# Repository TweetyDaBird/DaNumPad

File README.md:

## Notice!!! 
#### DaNumPad is currently under active development! Clone/Build at your own peril! Update will follow when the design has been fully build-tested!

# DaNumPad
A 'family' of mechanical numpad/macro pads that can be configured either as a classic 17-key numpad, or as a 20 key (5x4) macro pad.

- USB-C connector
- Cherry MX compatible switches
- Kailh Hotswap sockets
- Supports PCB-mounted Cherry style stabilizers
- Designed as a companion to most 60% keyboards, being the same 5 row 'height'.
- Sandwich case with top and bottom plate from FR4 material.
- Full SMD design, adapted to easily allow both SMT manufacturing and handsoldering.

## DaNumPad unWired & DaNumPad Glow
Available as two variations, wired and wireless with identical footprint, using the same plate but different PCB.

#### DaNumPad 17 Glow
- Classic 17-Key Numpad layout
- Atmega32u4 MCU
- Full Per-Key RGB
- QMK compatible

#### DaNumPad 20 Glow
- 20-Key macropad with two optional spots for rotary encoders.
- Atmega32u4 MCU
- Full Per-Key RGB
- QMK compatible

#### DaNumPad unWired
- 20-Key macropad with two optional spots for rotary encoders.
- Optional 17-Key layout on the same PCB (Requires soldering hotswap sockets on alternate placing)
- Wireless using an nRF85420 MCU
- ZMK compatible (Bluetooth)
- Can use a QMK compatible, 2.4Ghz Wireless dongle for lower latency/battery consumption. (Under development!)

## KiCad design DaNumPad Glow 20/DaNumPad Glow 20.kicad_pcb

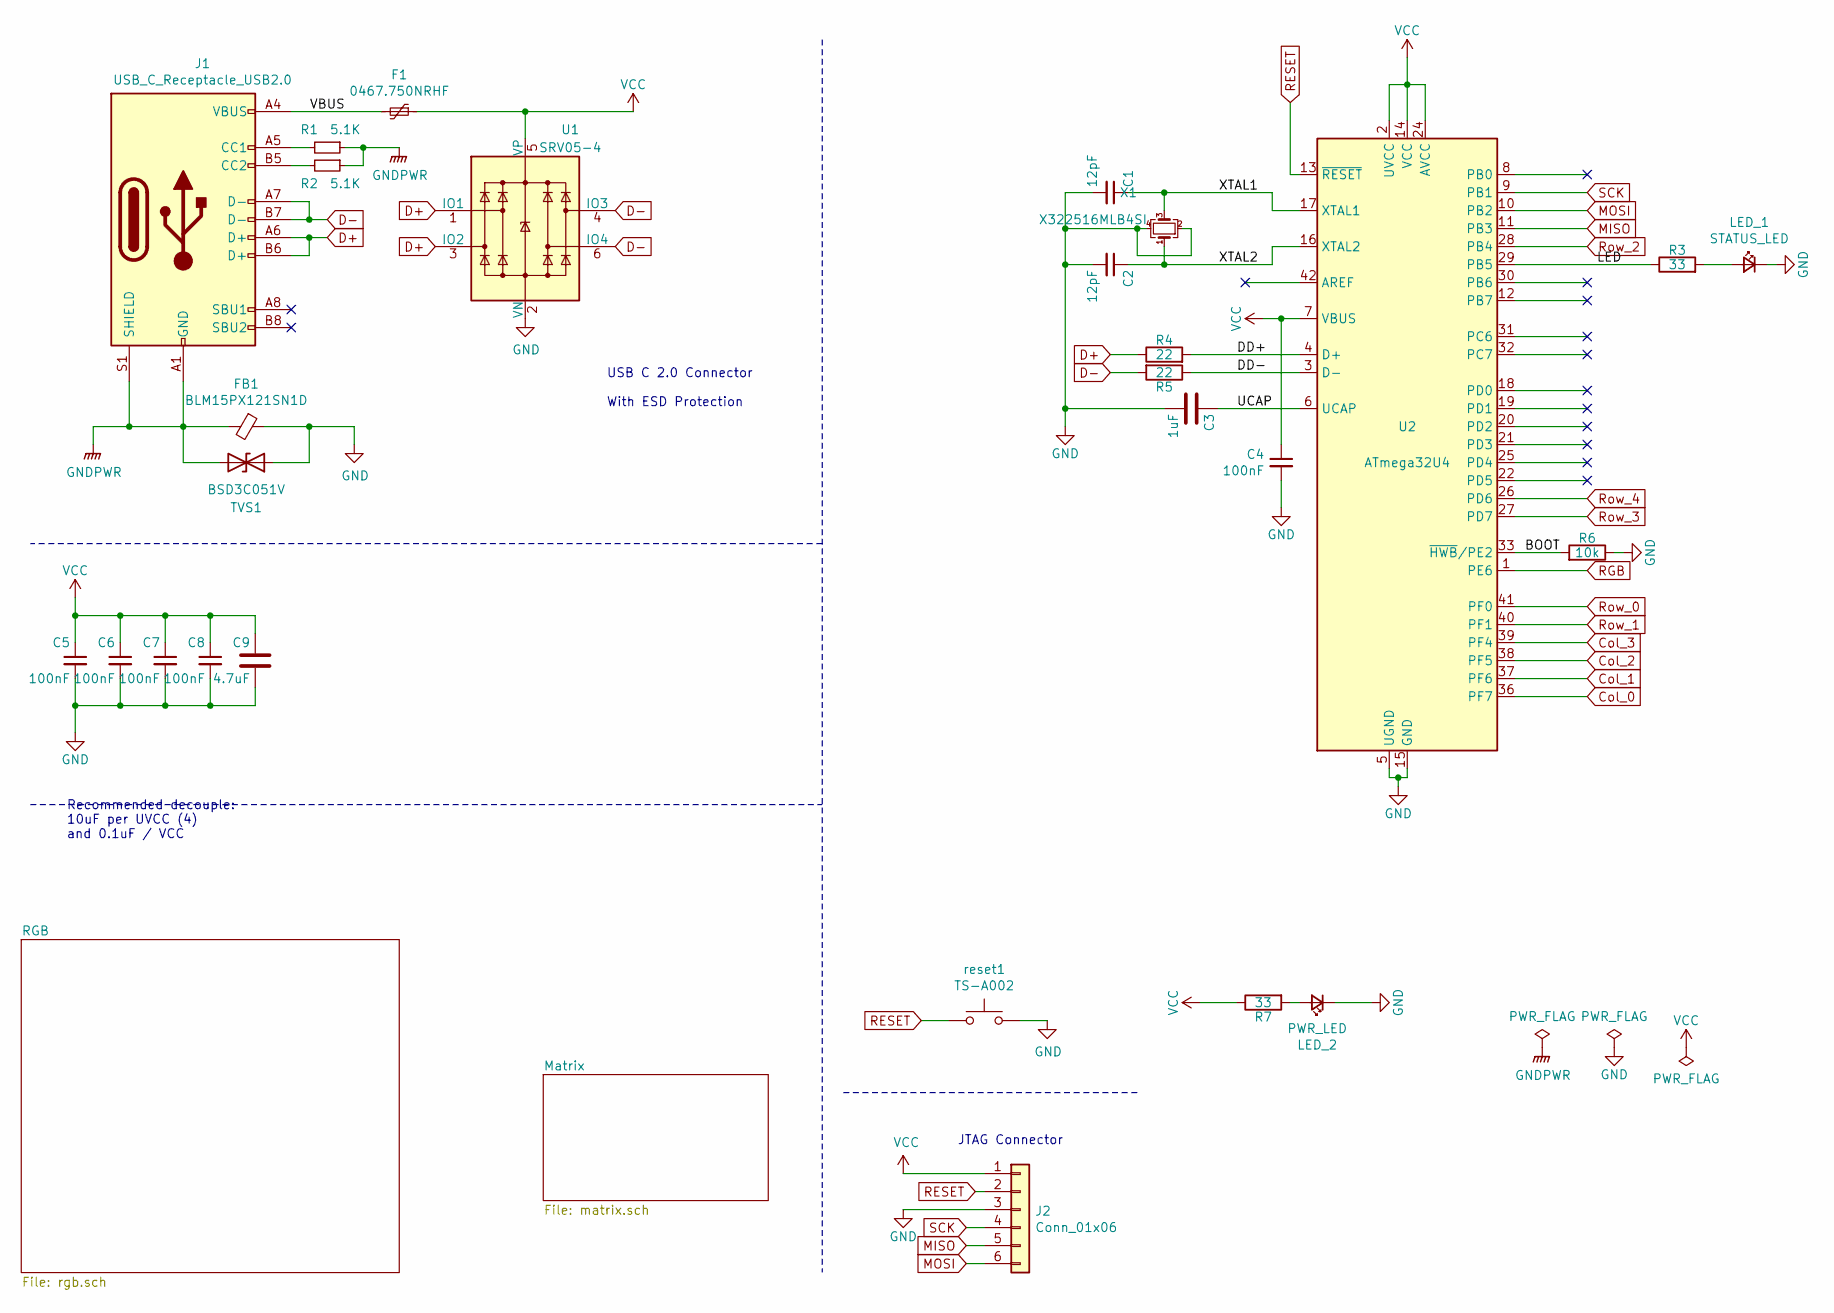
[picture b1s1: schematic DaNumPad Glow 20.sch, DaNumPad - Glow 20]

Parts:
C1, C2: 12pF; C_0603_1608Metric; Manufacturer_Part_Number CL10C120JB8NNNC; Mouser Part Number 581-06035A220J
C3: 1uF; C_0805_2012Metric; Manufacturer_Part_Number CL21B105KBFNNNE; Mouser Part Number 187-CL21B105KBFNNNG
C4, C5, C6, C7, C8: 100nF; C_0603_1608Metric; Manufacturer_Part_Number CC0603KRX7R9BB104; Mouser Part Number 581-06035C104JAT2A
C9: 4.7uF; C_0805_2012Metric; Manufacturer_Part_Number CL21A475KAQNNNE; Mouser Part Number 810-C2012X7R475K125C
F1: 0467.750NRHF; Fuse_0603_1608Metric_Castellated; Manufacturer_Part_Number 0467.750NRHF; LCSC C206991
FB1: BLM15PX121SN1D; R_0402_1005Metric_Pad0.72x0.64mm_HandSolder; Manufacturer_Part_Number BLM15PX121SN1D11; LCSC C88970
J1: USB_C_Receptacle_USB2.0; USB_C_Receptacle_HRO_TYPE-C-31-M-12; Manufacturer_Part_Number TYPE-C-31-M-12; LCSC C165948
J2: Conn_01x06; PinHeader_2x03_P2.54mm_Vertical
LED_1: STATUS_LED; LED_0603_1608Metric; Manufacturer_Part_Number KT-0603R; Mouser Part Number 604-APT1608EC
LED_2: PWR_LED; LED_0603_1608Metric; Manufacturer_Part_Number KT-0603R; Mouser Part Number 604-APT1608EC
R1, R2: 5.1K; R_0603_1608Metric; Manufacturer_Part_Number 0603WAF5101T5E; LCSC C23186
R3, R7: 33; R_0603_1608Metric; Manufacturer_Part_Number 0603WAF330JT5E; Mouser Part Number 667-ERJ-3EKF33R0V
R4, R5: 22; R_0603_1608Metric; Manufacturer_Part_Number 0603WAF220JT5E; Mouser Part Number 667-ERJ-3GEYJ220V
R6: 10k; R_0603_1608Metric; Manufacturer_Part_Number 0603WAF1002T5E; Mouser Part Number 667-ERJ-3GEYJ103V
TVS1: BSD3C051V; D_SOD-323; Manufacturer_Part_Number BSD3C051V; LCSC C151996
U1: SRV05-4; SOT-23-6; Manufacturer_Part_Number SRV05-4-P-T7; LCSC C85364
U2: ATmega32U4; QFN-44-1EP_7x7mm_P0.5mm_EP5.15x5.15mm; Manufacturer_Part_Number ATMEGA32U4-MU; Mouser Part Number 556-ATMEGA32U4RC-MU
X1: X322516MLB4SI; Crystal_SMD_3225-4Pin_3.2x2.5mm_HandSoldering; Mouser Part Number 81-XRCGB16M000FXN00R
reset1: TS-A002; SW_SPST_CK_RS282G05A3

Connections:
/BOOT: R6.2, U2.33 (~HWB~/PE2)
/DD+: R4.2, U2.4 (D+)
/DD-: R5.1, U2.3 (D-)
/LED: R3.1, U2.29 (PB5)
/UCAP: C3.1, U2.6 (UCAP)
/VBUS: F1.2, J1.A4 (VBUS), J1.A9 (VBUS), J1.B4 (VBUS), J1.B9 (VBUS)
/XTAL1: C1.1, U2.17 (XTAL1), X1.3
/XTAL2: C2.1, U2.16 (XTAL2), X1.1
Col_0: U2.36 (PF7); also elsewhere on the board
Col_1: U2.37 (PF6); also elsewhere on the board
Col_2: U2.38 (PF5); also elsewhere on the board
D+: J1.A6 (D+), J1.B6 (D+), R4.1, U1.1 (IO1), U1.3 (IO2)
D-: J1.A7 (D-), J1.B7 (D-), R5.2, U1.4 (IO3), U1.6 (IO4)
GND: C1.2, C2.2, C3.2, C4.2, C5.2, C6.2, C7.2, C8.2, C9.2, FB1.1, J2.3, LED_1.1 (K), LED_2.1 (K), R6.1, TVS1.1 (A1), U1.2 (VN), U2.5 (UGND), U2.15 (GND), U2.23 (GND), U2.35 (GND), U2.43 (GND), X1.2, X1.4, reset1.2; also elsewhere on the board
GNDPWR: FB1.2, J1.A1 (GND), J1.A12 (GND), J1.B1 (GND), J1.B12 (GND), J1.S1 (SHIELD), R1.1, R2.1, TVS1.2 (A2)
MISO: J2.5, U2.11 (PB3)
MOSI: J2.6, U2.10 (PB2)
unnamed: J1.A5 (CC1), R1.2
unnamed: J1.B5 (CC2), R2.2
unnamed: LED_1.2 (A), R3.2
unnamed: LED_2.2 (A), R7.2
RESET: J2.2, U2.13 (~RESET), reset1.1
RGB: U2.1 (PE6); also elsewhere on the board
Row_0: U2.41 (PF0); also elsewhere on the board
Row_1: U2.40 (PF1); also elsewhere on the board
Row_2: U2.28 (PB4); also elsewhere on the board
Row_3: U2.27 (PD7); also elsewhere on the board
Row_4: U2.26 (PD6); also elsewhere on the board
SCK: J2.4, U2.9 (PB1)
VCC: C4.1, C5.1, C6.1, C7.1, C8.1, C9.1, F1.1, J2.1, R7.1, U1.5 (VP), U2.2 (UVCC), U2.7 (VBUS), U2.14 (VCC), U2.24 (AVCC), U2.34 (VCC), U2.44 (AVCC); also elsewhere on the board

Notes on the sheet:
USB C 2.0 Connector With ESD Protection
Recommended decouple: 10uF per UVCC (4) and 0.1uF / VCC
JTAG Connector

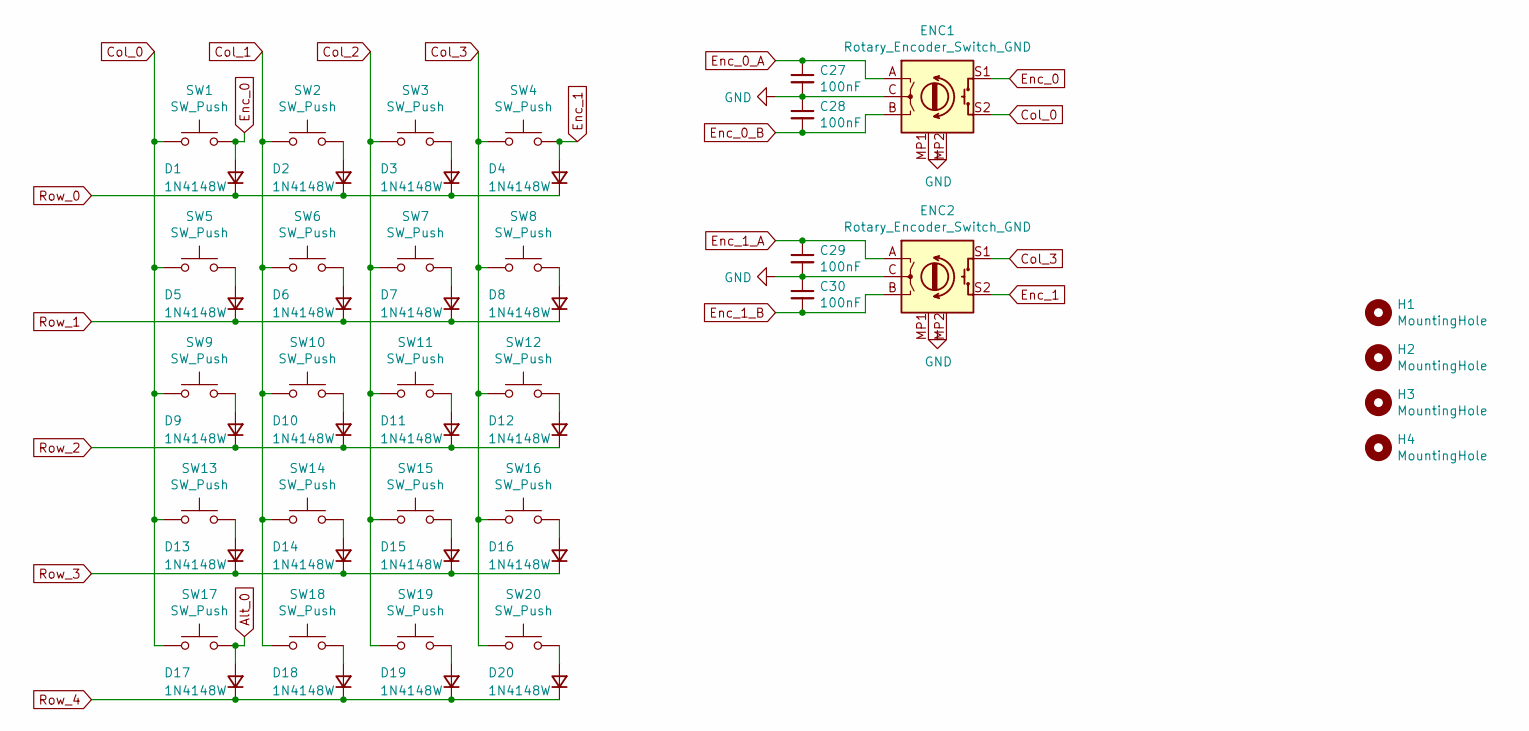
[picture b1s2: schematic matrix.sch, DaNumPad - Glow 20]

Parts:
C27, C28, C29, C30: 100nF; C_0603_1608Metric; Manufacturer_Part_Number CC0603KRX7R9BB104; LCSC C14663
D1, D2, D3, D4, D5, D6, D7, D8, D9, D10, D11, D12, D13, D14, D15, D16, D17, D18, D19, D20: 1N4148W; D_SOD-123; Manufacturer_Part_Number 1N4148W; LCSC C81598
ENC1, ENC2: Rotary_Encoder_Switch_GND; RotaryEncoder_Alps_EC11E-Switch_Vertical_H20mm
H1, H2, H3, H4: MountingHole; MountingHole_3.7mm
SW1, SW2, SW3, SW4, SW5, SW6, SW7, SW8, SW9, SW10, SW11, SW12, SW13, SW14, SW15, SW16, SW17, SW18, SW19, SW20: SW_Push; Kailh_socket_MX_RGB

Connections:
Alt_0: D17.2 (A), SW17.2
Col_0: ENC1.S2, SW1.1, SW5.1, SW9.1, SW13.1, SW17.1; also elsewhere on the board
Col_1: SW2.1, SW6.1, SW10.1, SW14.1, SW18.1; also elsewhere on the board
Col_2: SW3.1, SW7.1, SW11.1, SW15.1, SW19.1; also elsewhere on the board
Enc_0: D1.2 (A), ENC1.S1, SW1.2
Enc_0_A: C27.1, ENC1.A
Enc_0_B: C28.2, ENC1.B
Enc_1_A: C29.1, ENC2.A
Enc_1_B: C30.2, ENC2.B
GND: C27.2, C28.1, C29.2, C30.1, ENC1.C, ENC1.MP2 (GND), ENC2.C, ENC2.MP2 (GND); also elsewhere on the board
unnamed: D2.2 (A), SW2.2
unnamed: D3.2 (A), SW3.2
unnamed: D5.2 (A), SW5.2
unnamed: D6.2 (A), SW6.2
unnamed: D7.2 (A), SW7.2
unnamed: D9.2 (A), SW9.2
unnamed: D10.2 (A), SW10.2
unnamed: D11.2 (A), SW11.2
unnamed: D12.2 (A), SW12.2
unnamed: D13.2 (A), SW13.2
unnamed: D14.2 (A), SW14.2
unnamed: D15.2 (A), SW15.2
unnamed: D18.2 (A), SW18.2
unnamed: D19.2 (A), SW19.2
unnamed: D20.2 (A), SW20.2
Row_0: D1.1 (K), D2.1 (K), D3.1 (K), D4.1 (K); also elsewhere on the board
Row_1: D5.1 (K), D6.1 (K), D7.1 (K), D8.1 (K); also elsewhere on the board
Row_2: D9.1 (K), D10.1 (K), D11.1 (K), D12.1 (K); also elsewhere on the board
Row_3: D13.1 (K), D14.1 (K), D15.1 (K), D16.1 (K); also elsewhere on the board
Row_4: D17.1 (K), D18.1 (K), D19.1 (K), D20.1 (K); also elsewhere on the board

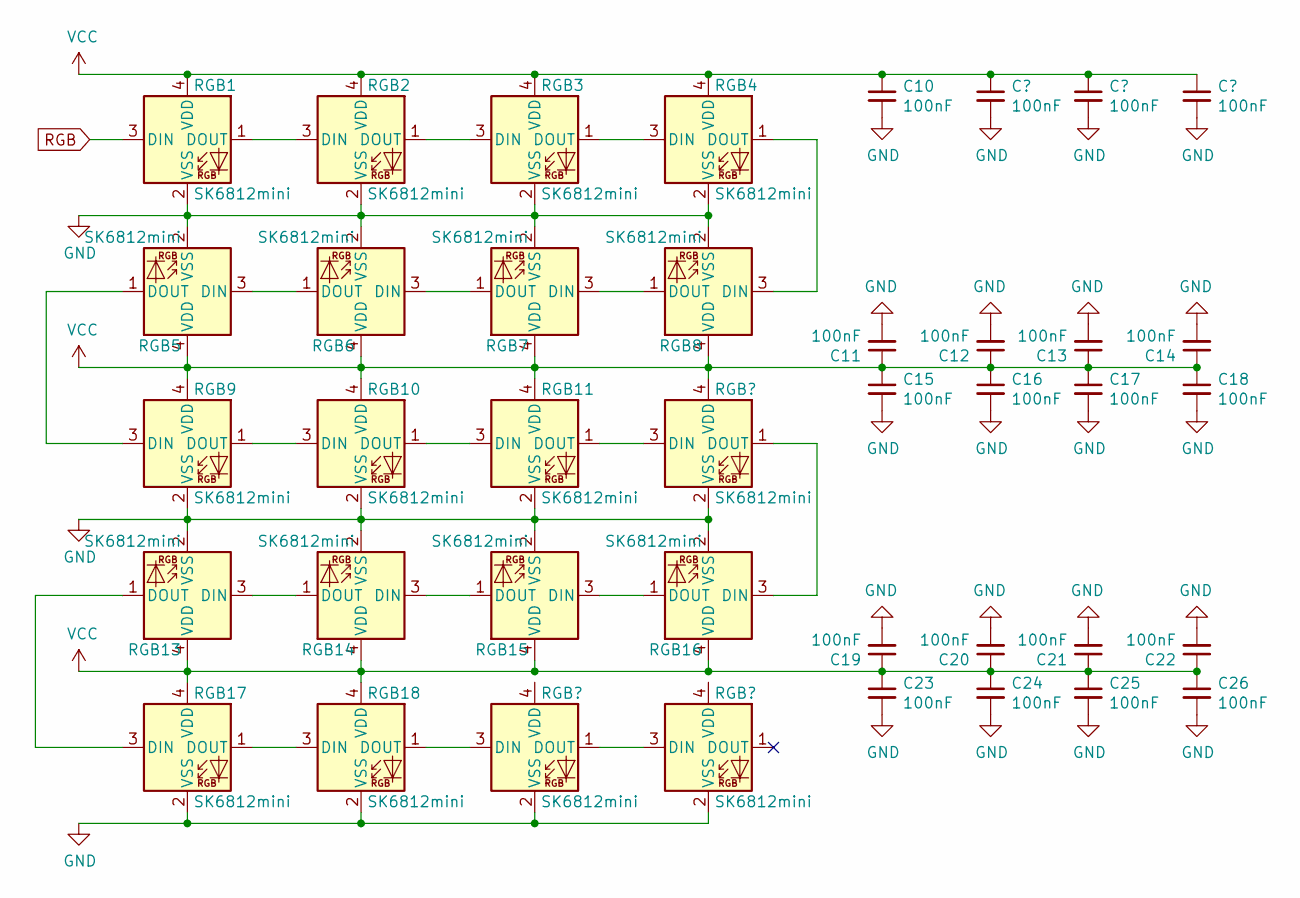
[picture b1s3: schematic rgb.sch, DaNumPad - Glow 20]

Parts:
C10, C11, C12, C13, C14, C15, C16, C17, C18, C19, C20, C21, C22, C23, C24, C25, C26: 100nF; C_0603_1608Metric; Manufacturer_Part_Number CC0603KRX7R9BB104; LCSC C14663
RGB1, RGB2, RGB3, RGB4, RGB5, RGB6, RGB7, RGB8, RGB9, RGB10, RGB11, RGB13, RGB14, RGB15, RGB16, RGB17, RGB18: SK6812mini; SK6812MINI_Midmount

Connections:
GND: C10.2, C11.2, C12.2, C13.2, C14.2, C15.2, C16.2, C17.2, C18.2, C19.2, C20.2, C21.2, C22.2, C23.2, C24.2, C25.2, C26.2, RGB1.2 (VSS), RGB2.2 (VSS), RGB3.2 (VSS), RGB4.2 (VSS), RGB5.2 (VSS), RGB6.2 (VSS), RGB7.2 (VSS), RGB8.2 (VSS), RGB9.2 (VSS), RGB10.2 (VSS), RGB11.2 (VSS), RGB13.2 (VSS), RGB14.2 (VSS), RGB15.2 (VSS), RGB16.2 (VSS), RGB17.2 (VSS), RGB18.2 (VSS); also elsewhere on the board
unnamed: RGB1.1 (DOUT), RGB2.3 (DIN)
unnamed: RGB2.1 (DOUT), RGB3.3 (DIN)
unnamed: RGB3.1 (DOUT), RGB4.3 (DIN)
unnamed: RGB4.1 (DOUT), RGB8.3 (DIN)
unnamed: RGB5.1 (DOUT), RGB9.3 (DIN)
unnamed: RGB5.3 (DIN), RGB6.1 (DOUT)
unnamed: RGB6.3 (DIN), RGB7.1 (DOUT)
unnamed: RGB7.3 (DIN), RGB8.1 (DOUT)
unnamed: RGB10.1 (DOUT), RGB11.3 (DIN)
unnamed: RGB9.1 (DOUT), RGB10.3 (DIN)
unnamed 52: RGB11.1 (DOUT); also elsewhere on the board
unnamed 53: RGB16.3 (DIN); also elsewhere on the board
unnamed: RGB13.1 (DOUT), RGB17.3 (DIN)
unnamed: RGB13.3 (DIN), RGB14.1 (DOUT)
unnamed: RGB14.3 (DIN), RGB15.1 (DOUT)
unnamed: RGB15.3 (DIN), RGB16.1 (DOUT)
unnamed: RGB17.1 (DOUT), RGB18.3 (DIN)
unnamed 59: RGB18.1 (DOUT); also elsewhere on the board
RGB: RGB1.3 (DIN); also elsewhere on the board
VCC: C10.1, C11.1, C12.1, C13.1, C14.1, C15.1, C16.1, C17.1, C18.1, C19.1, C20.1, C21.1, C22.1, C23.1, C24.1, C25.1, C26.1, RGB1.4 (VDD), RGB2.4 (VDD), RGB3.4 (VDD), RGB4.4 (VDD), RGB5.4 (VDD), RGB6.4 (VDD), RGB7.4 (VDD), RGB8.4 (VDD), RGB9.4 (VDD), RGB10.4 (VDD), RGB11.4 (VDD), RGB13.4 (VDD), RGB14.4 (VDD), RGB15.4 (VDD), RGB16.4 (VDD), RGB17.4 (VDD), RGB18.4 (VDD); also elsewhere on the board

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
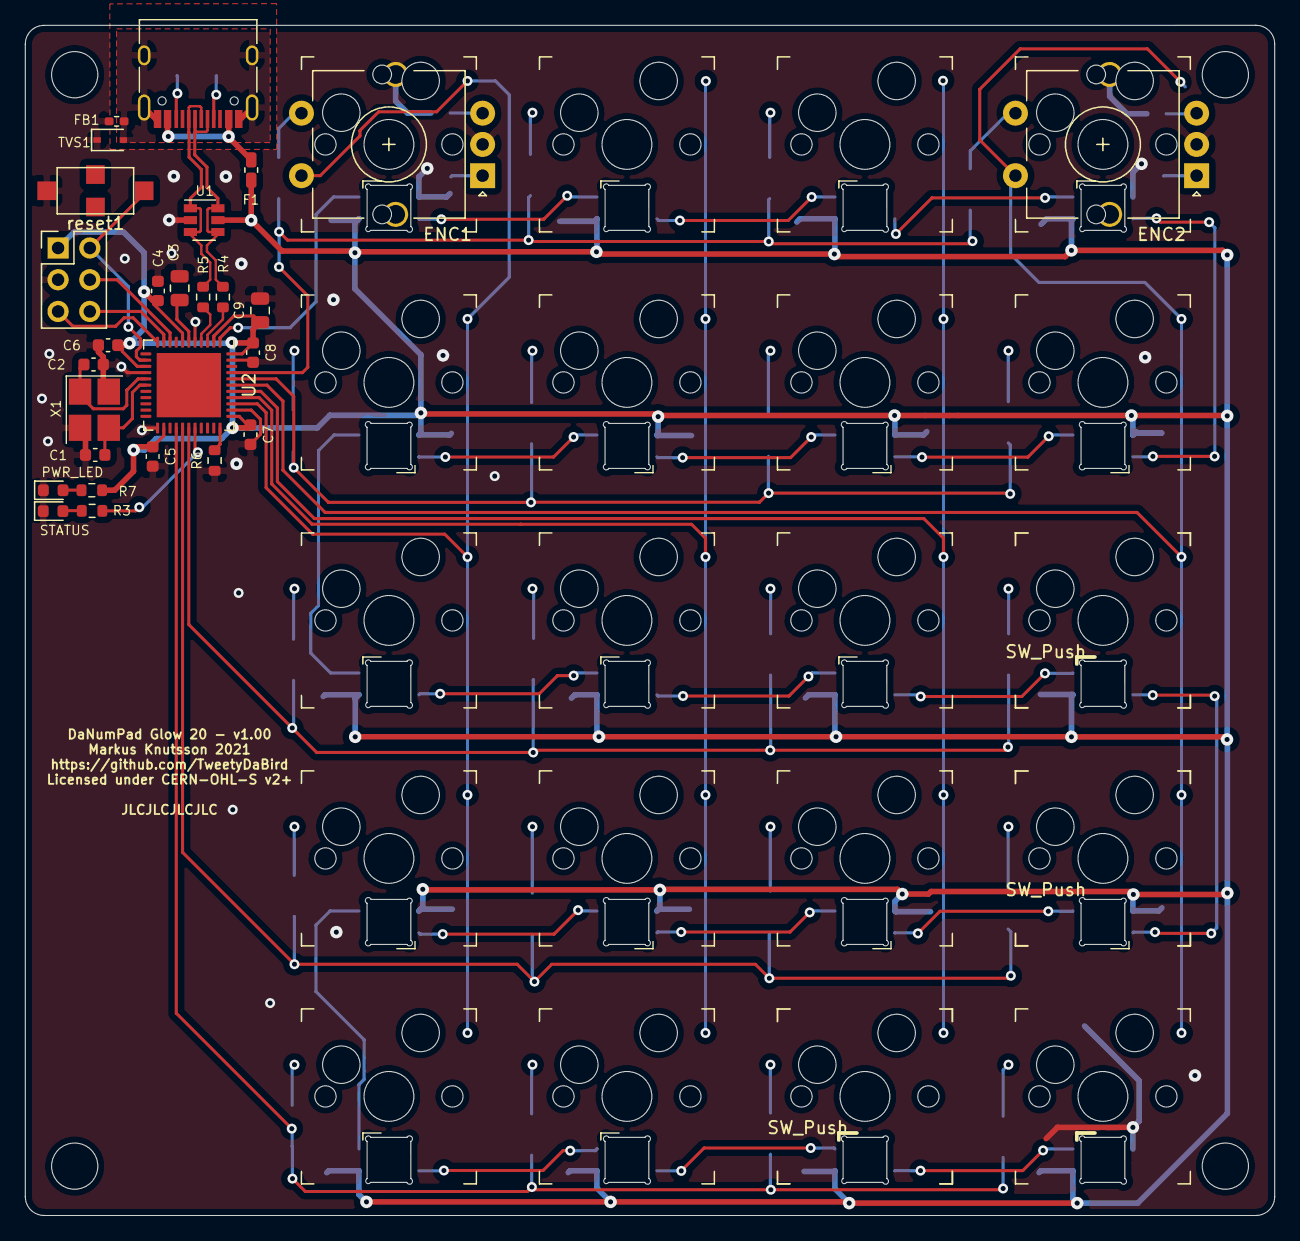
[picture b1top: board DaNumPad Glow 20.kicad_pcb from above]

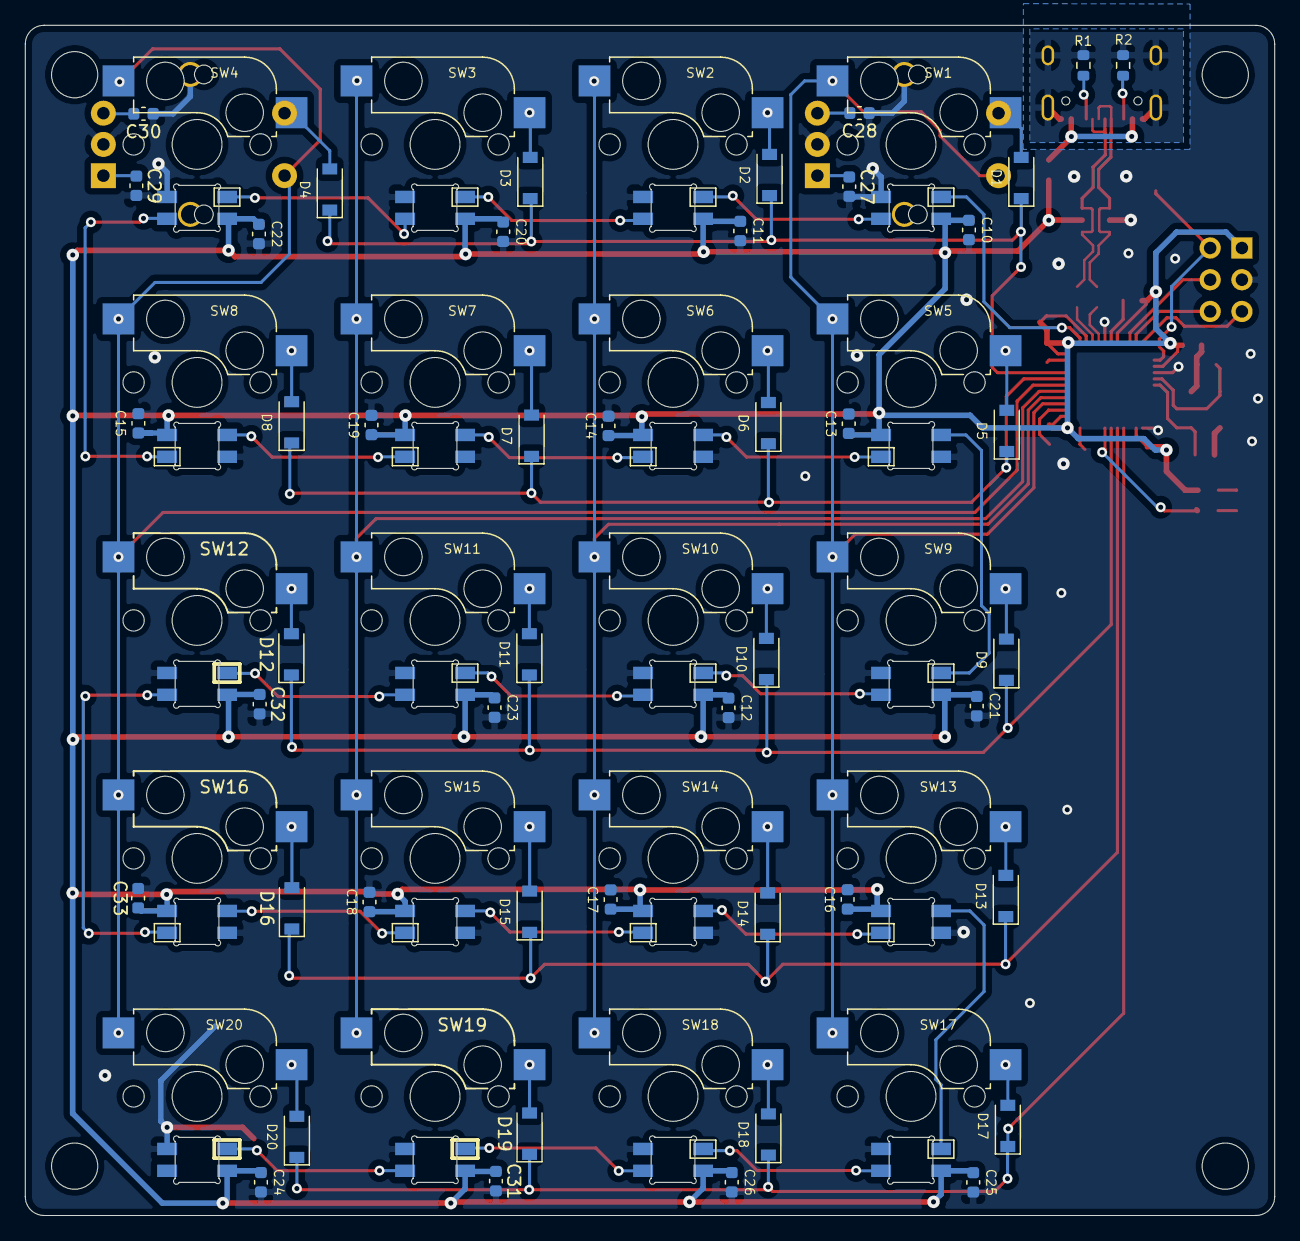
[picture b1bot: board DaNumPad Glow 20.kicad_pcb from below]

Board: 2 copper layers, 100.0 x 95.3 mm, 117 parts (46 on the bottom side), 74 nets.

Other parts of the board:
C31, C32, C33: 100nF; C_0603_1608Metric
RGB12, RGB19, RGB20: SK6812mini; SK6812MINI_Midmount

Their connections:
GND: C31.2, C32.2, C33.2, RGB12.2, RGB19.2, RGB20.2; also elsewhere on the board
unnamed 52: RGB12.3; also elsewhere on the board
unnamed 53: RGB12.1; also elsewhere on the board
unnamed 59: RGB19.3; also elsewhere on the board
unnamed: RGB19.1, RGB20.3
VCC: C31.1, C32.1, C33.1, RGB12.4, RGB19.4, RGB20.4; also elsewhere on the board

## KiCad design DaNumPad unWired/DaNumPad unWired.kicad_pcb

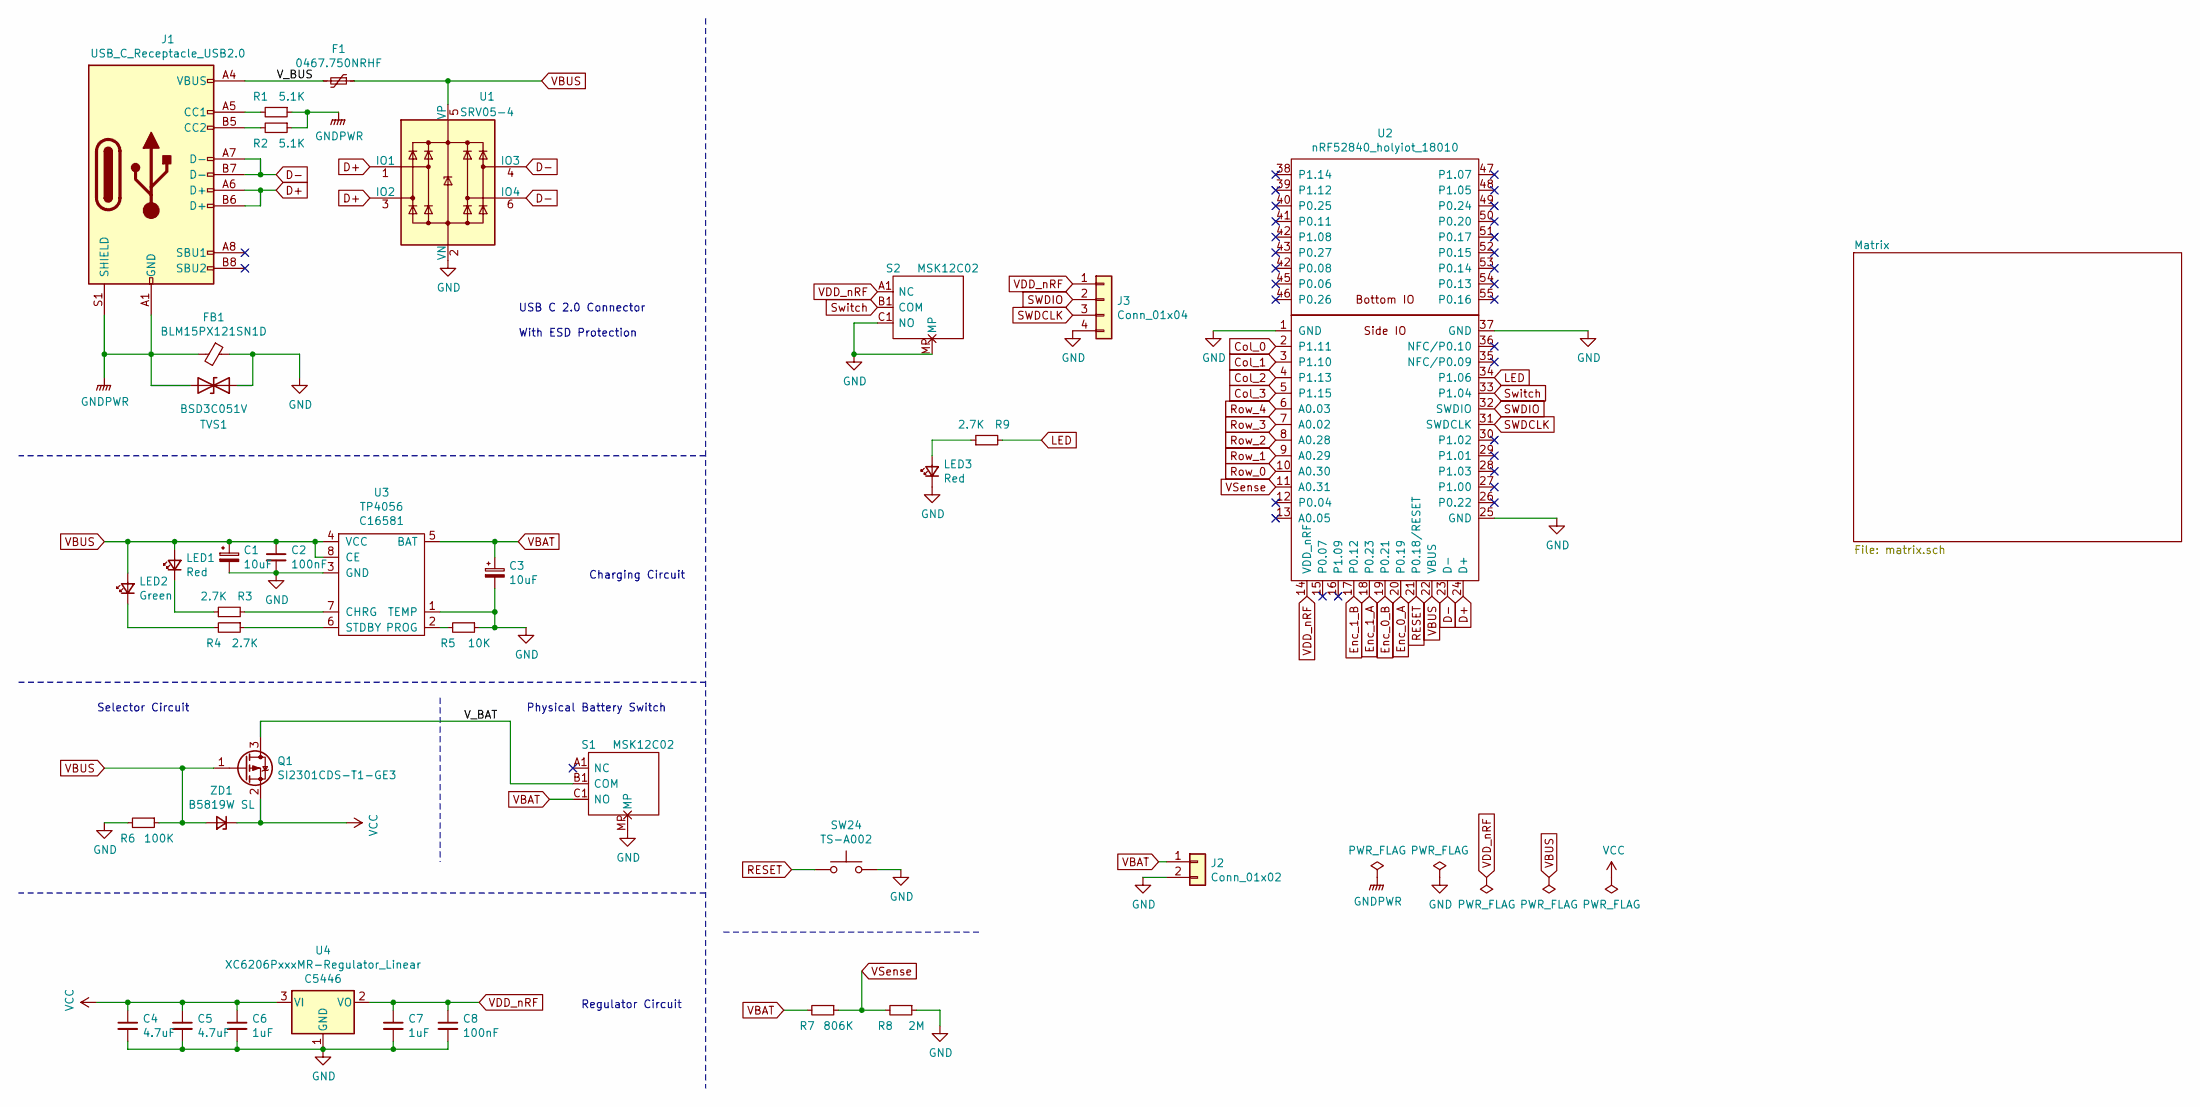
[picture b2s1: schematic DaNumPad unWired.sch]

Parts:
C1, C3: 10uF; CP_EIA-3216-18_Kemet-A; Manufacturer_Part_Number CA45-A-10V-10uF-M; LCSC C128256
C2, C8: 100nF; C_0603_1608Metric; Manufacturer_Part_Number CC0603KRX7R9BB104; LCSC C14663
C4, C5: 4.7uF; C_0603_1608Metric; Manufacturer_Part_Number CL10A475KO8NNNC; LCSC C19666
C6, C7: 1uF; C_0603_1608Metric; Manufacturer_Part_Number CL10A105KB8NNNC; LCSC C15849
F1: 0467.750NRHF; Fuse_0603_1608Metric_Castellated; Manufacturer_Part_Number 0467.750NRHF; LCSC C206991
FB1: BLM15PX121SN1D; R_0402_1005Metric_Pad0.72x0.64mm_HandSolder; Manufacturer_Part_Number BLM15PX121SN1D11; LCSC C882964
J1: USB_C_Receptacle_USB2.0; USB_C_Receptacle_HRO_TYPE-C-31-M-12; Manufacturer_Part_Number TYPE-C-31-M-12; LCSC C165948
J2: Conn_01x02; JST_PH_S2B-PH-K_1x02_P2.00mm_Horizontal; Manufacturer_Part_Number A2001WV-2P; LCSC C225188
J3: Conn_01x04; PinHeader_1x04_P2.54mm_Vertical
LED1, LED3: Red; LED_0603_1608Metric; Manufacturer_Part_Number KT-0603R; LCSC C2286
LED2: Green; LED_0603_1608Metric; Manufacturer_Part_Number 19-217/GHC-YR1S2/3T; LCSC C72043
Q1: SI2301CDS-T1-GE3; SOT-23; Manufacturer_Part_Number SI2301CDS-T1-GE3; LCSC C10487
R1, R2: 5.1K; R_0603_1608Metric; Manufacturer_Part_Number 0603WAF5101T5E; LCSC C23186
R3, R4, R9: 2.7K; R_0603_1608Metric; Manufacturer_Part_Number 0603WAF2701T5E; LCSC C13167
R5: 10K; R_0603_1608Metric; Manufacturer_Part_Number 0603WAF1002T5E; LCSC C25804
R6: 100K; R_0603_1608Metric; Manufacturer_Part_Number 0603WAF1003T5E; LCSC C25803
R7: 806K; R_0603_1608Metric; Manufacturer_Part_Number RMC0603806K1%N; LCSC C269512
R8: 2M; R_0603_1608Metric; Manufacturer_Part_Number 0603WAF2004T5E; LCSC C22976
S1, S2: MSK12C02; Manufacturer_Part_Number MSK12C02; LCSC C431540
SW24: TS-A002; SW_SPST_CK_RS282G05A3
TVS1: BSD3C051V; D_SOD-323; Manufacturer_Part_Number BSD3C051V; LCSC C151996
U1: SRV05-4; SOT-23-6; Manufacturer_Part_Number SRV05-4-P-T7; LCSC C85364
U2: nRF52840_holyiot_18010; nRF52840_holyiot_18010_HS_simple
U3: TP4056; SOIC127P600X175-9N; Manufacturer_Part_Number TP4056-42-ESOP8; LCSC C16581
U4: XC6206PxxxMR-Regulator_Linear; SOT-23; Manufacturer_Part_Number XC6206P332MR; LCSC C5446
ZD1: B5819W SL; D_SOD-123; Manufacturer_Part_Number B5819W SL; LCSC C8598

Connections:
/V_BAT: Q1.3 (D), S1.B1 (COM)
/V_BUS: F1.2, J1.A4 (VBUS), J1.A9 (VBUS), J1.B4 (VBUS), J1.B9 (VBUS)
Col_0: U2.2 (P1.11); also elsewhere on the board
Col_1: U2.3 (P1.10); also elsewhere on the board
Col_2: U2.4 (P1.13); also elsewhere on the board
Col_3: U2.5 (P1.15); also elsewhere on the board
D+: J1.A6 (D+), J1.B6 (D+), U1.1 (IO1), U1.3 (IO2), U2.24 (D+)
D-: J1.A7 (D-), J1.B7 (D-), U1.4 (IO3), U1.6 (IO4), U2.23 (D-)
Enc_0_A: U2.20 (P0.19); also elsewhere on the board
Enc_0_B: U2.19 (P0.21); also elsewhere on the board
Enc_1_A: U2.18 (P0.23); also elsewhere on the board
Enc_1_B: U2.17 (P0.12); also elsewhere on the board
GND: C1.2, C2.2, C3.2, C4.2, C5.2, C6.2, C7.2, C8.2, FB1.1, J2.2, J3.4, LED3.1 (K), R5.1, R6.2, R8.1, S1.MP, S2.C1 (NO), S2.MP, SW24.2, TVS1.1 (A1), U1.2 (VN), U2.1 (GND), U2.25 (GND), U2.37 (GND), U3.1 (TEMP), U3.3 (GND), U4.1 (GND); also elsewhere on the board
GNDPWR: FB1.2, J1.A1 (GND), J1.A12 (GND), J1.B1 (GND), J1.B12 (GND), J1.S1 (SHIELD), R1.1, R2.1, TVS1.2 (A2)
LED: R9.2, U2.34 (P1.06)
unnamed: J1.A5 (CC1), R1.2
unnamed: J1.B5 (CC2), R2.2
unnamed: LED1.1 (K), R3.1
unnamed: LED2.1 (K), R4.2
unnamed: LED3.2 (A), R9.1
unnamed: R3.2, U3.7 (CHRG)
unnamed: R4.1, U3.6 (STDBY)
unnamed: R5.2, U3.2 (PROG)
RESET: SW24.1, U2.21 (P0.18/RESET)
Row_0: U2.10 (A0.30); also elsewhere on the board
Row_1: U2.9 (A0.29); also elsewhere on the board
Row_2: U2.8 (A0.28); also elsewhere on the board
Row_3: U2.7 (A0.02); also elsewhere on the board
Row_4: U2.6 (A0.03); also elsewhere on the board
SWDCLK: J3.3, U2.31 (SWDCLK)
SWDIO: J3.2, U2.32 (SWDIO)
Switch: S2.B1 (COM), U2.33 (P1.04)
VBAT: C3.1, J2.1, R7.2, S1.C1 (NO), U3.5 (BAT)
VBUS: C1.1, C2.1, F1.1, LED1.2 (A), LED2.2 (A), Q1.1 (G), R6.1, U1.5 (VP), U2.22 (VBUS), U3.4 (VCC), U3.8 (CE), ZD1.2 (A)
VCC: C4.1, C5.1, C6.1, Q1.2 (S), U4.3 (VI), ZD1.1 (K)
VDD_nRF: C7.1, C8.1, J3.1, S2.A1 (NC), U2.14 (VDD_nRF), U4.2 (VO)
VSense: R7.1, R8.2, U2.11 (A0.31)

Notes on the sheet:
Selector Circuit
Physical Battery Switch
Charging Circuit
Regulator Circuit
USB C 2.0 Connector With ESD Protection

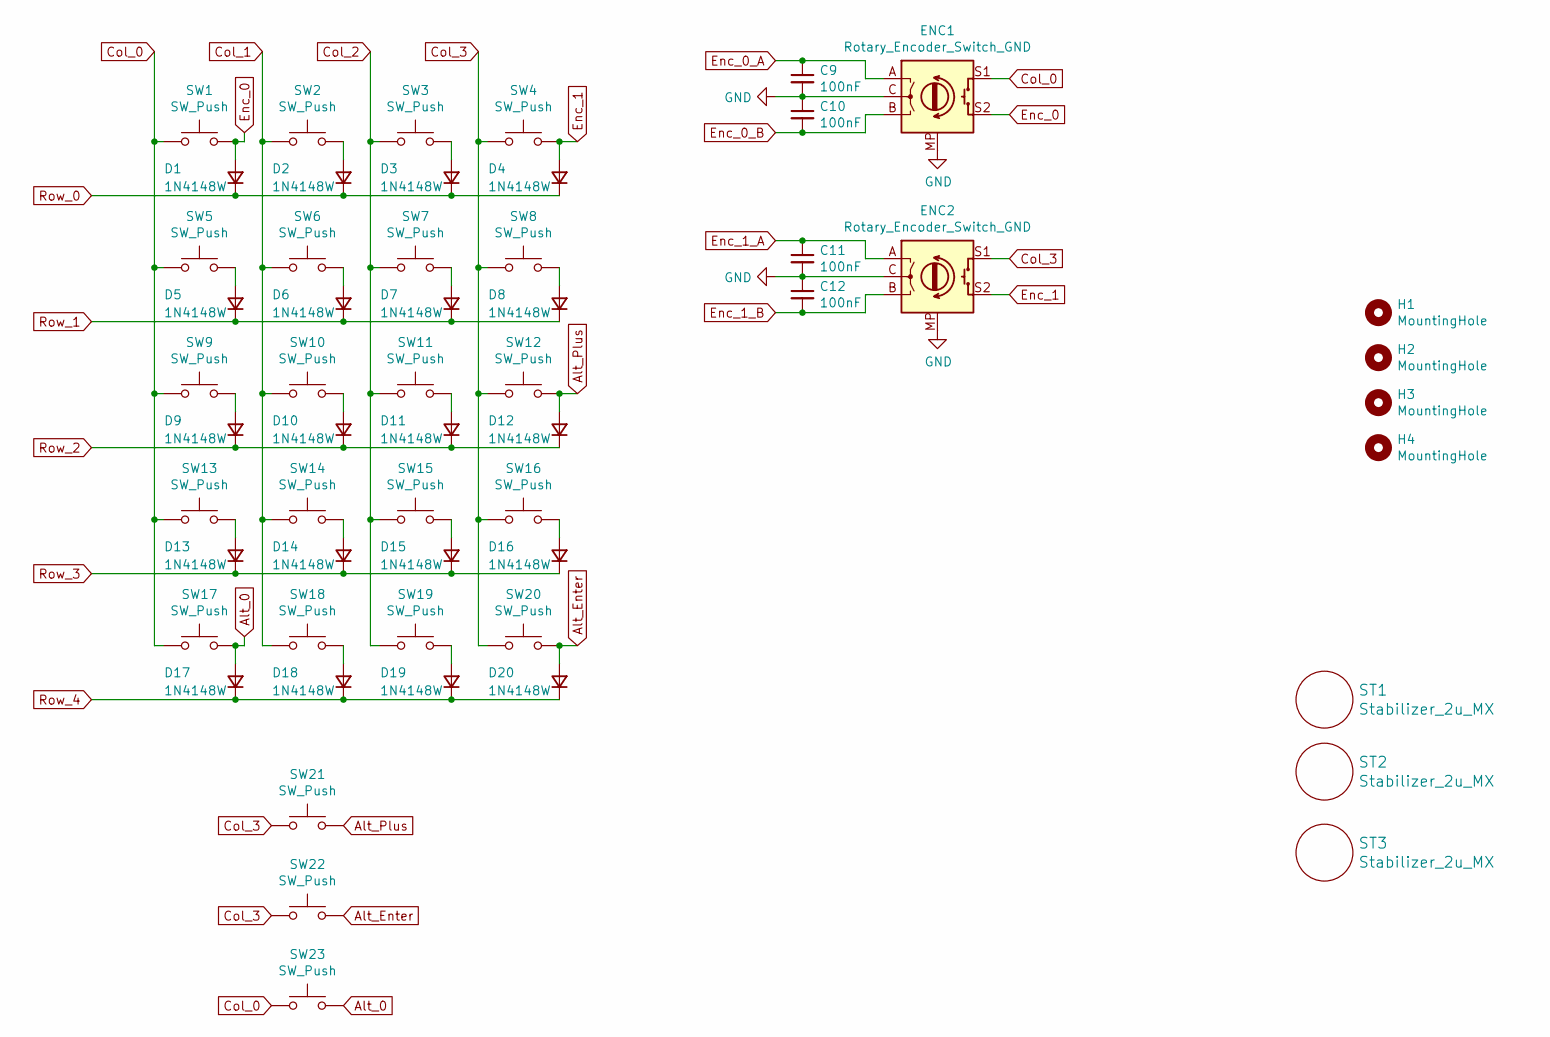
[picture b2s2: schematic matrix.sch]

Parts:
C9, C10, C11, C12: 100nF; C_0603_1608Metric; Manufacturer_Part_Number CC0603KRX7R9BB104; LCSC C14663
D1, D2, D3, D4, D5, D6, D7, D8, D9, D10, D11, D12, D13, D14, D15, D16, D17, D18, D19, D20: 1N4148W; D_SOD-123; Manufacturer_Part_Number 1N4148W; LCSC C81598
ENC1, ENC2: Rotary_Encoder_Switch_GND; RotaryEncoder_Alps_EC11E-Switch_Vertical_H20mm
H1, H2, H3, H4: MountingHole; MountingHole_3.7mm
ST1, ST2, ST3: Stabilizer_2u_MX; Stabilizer_MX_2u
SW1, SW2, SW3, SW4, SW5, SW6, SW7, SW8, SW9, SW10, SW11, SW12, SW13, SW14, SW15, SW16, SW17, SW18, SW19, SW20, SW21, SW22, SW23: SW_Push; Kailh_socket_MX_RGB

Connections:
Alt_0: D17.2 (A), SW17.2, SW23.2
Alt_Enter: D20.2 (A), SW20.2, SW22.1
Alt_Plus: D12.2 (A), SW12.2, SW21.1
Col_0: ENC1.S1, SW1.1, SW5.1, SW9.1, SW13.1, SW17.1, SW23.1; also elsewhere on the board
Col_1: SW2.1, SW6.1, SW10.1, SW14.1, SW18.1; also elsewhere on the board
Col_2: SW3.1, SW7.1, SW11.1, SW15.1, SW19.1; also elsewhere on the board
Col_3: ENC2.S1, SW4.1, SW8.2, SW12.1, SW16.2, SW20.1, SW21.2, SW22.2; also elsewhere on the board
Enc_0: D1.2 (A), ENC1.S2, SW1.2
Enc_0_A: C9.1, ENC1.A; also elsewhere on the board
Enc_0_B: C10.2, ENC1.B; also elsewhere on the board
Enc_1: D4.2 (A), ENC2.S2, SW4.2
Enc_1_A: C11.1, ENC2.A; also elsewhere on the board
Enc_1_B: C12.2, ENC2.B; also elsewhere on the board
GND: C9.2, C10.1, C11.2, C12.1, ENC1.C, ENC1.MP (GND), ENC2.C, ENC2.MP (GND); also elsewhere on the board
unnamed: D2.2 (A), SW2.2
unnamed: D3.2 (A), SW3.2
unnamed: D5.2 (A), SW5.2
unnamed: D6.2 (A), SW6.2
unnamed: D7.2 (A), SW7.2
unnamed: D8.2 (A), SW8.1
unnamed: D9.2 (A), SW9.2
unnamed: D10.2 (A), SW10.2
unnamed: D11.2 (A), SW11.2
unnamed: D13.2 (A), SW13.2
unnamed: D14.2 (A), SW14.2
unnamed: D15.2 (A), SW15.2
unnamed: D16.2 (A), SW16.1
unnamed: D18.2 (A), SW18.2
unnamed: D19.2 (A), SW19.2
Row_0: D1.1 (K), D2.1 (K), D3.1 (K), D4.1 (K); also elsewhere on the board
Row_1: D5.1 (K), D6.1 (K), D7.1 (K), D8.1 (K); also elsewhere on the board
Row_2: D9.1 (K), D10.1 (K), D11.1 (K), D12.1 (K); also elsewhere on the board
Row_3: D13.1 (K), D14.1 (K), D15.1 (K), D16.1 (K); also elsewhere on the board
Row_4: D17.1 (K), D18.1 (K), D19.1 (K), D20.1 (K); also elsewhere on the board

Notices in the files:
DaNumPad Glow 20/DaNumPad Glow 20.kicad_pcb:
Licensed under CERN-OHL-S v2 or superseding version
